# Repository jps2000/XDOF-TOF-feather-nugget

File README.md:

# XDOF-TOF-feather-nugget
Feather nugget (piggyback PCB)  with BNO080/BNO055 IMU BMP388 Baro and VL53L1X tof sensor

Small PCB that fits to feather interface. Tested with nrf52832 BLE4.2
Features
-	9DOF IMU BNO080 or BNO055 optional
-	BMP388  Sensor for height measurements
-	TOF sensor VL53L1X up to 4 meters
-	1 neopixel status LED
-	ON/ OFF toggle button for battery use; USB auto on, shtdown from controller
-	Fits inside the feather footprint

Open source hardware, producers and suggestions welcome

feather nrf52832:  To achieve lowest battery current in off it is recommendend to remove the 100k pullup on EN (R5) and to replace the MBR120 shottky diode (D5) by a SI diode (1N4148).

The housing (not for TOF sensors)  is 3D printed. The cover should be made of transparent or translucent materials Use four screws ,Flat head, stainless steel 16mm long 2.2 mm diameter. The  battery is a Lipo size 502035 with 350mAh. Attention: wrong battery polarity destroys the feather. (Top view feather : GND = left VCC  = right)
Use a Kapton tape and double glue tape between the feather board and the battery.
The button can be made of a 2mm nylon Cylinder head screw colored with an Edding 3000 pen.

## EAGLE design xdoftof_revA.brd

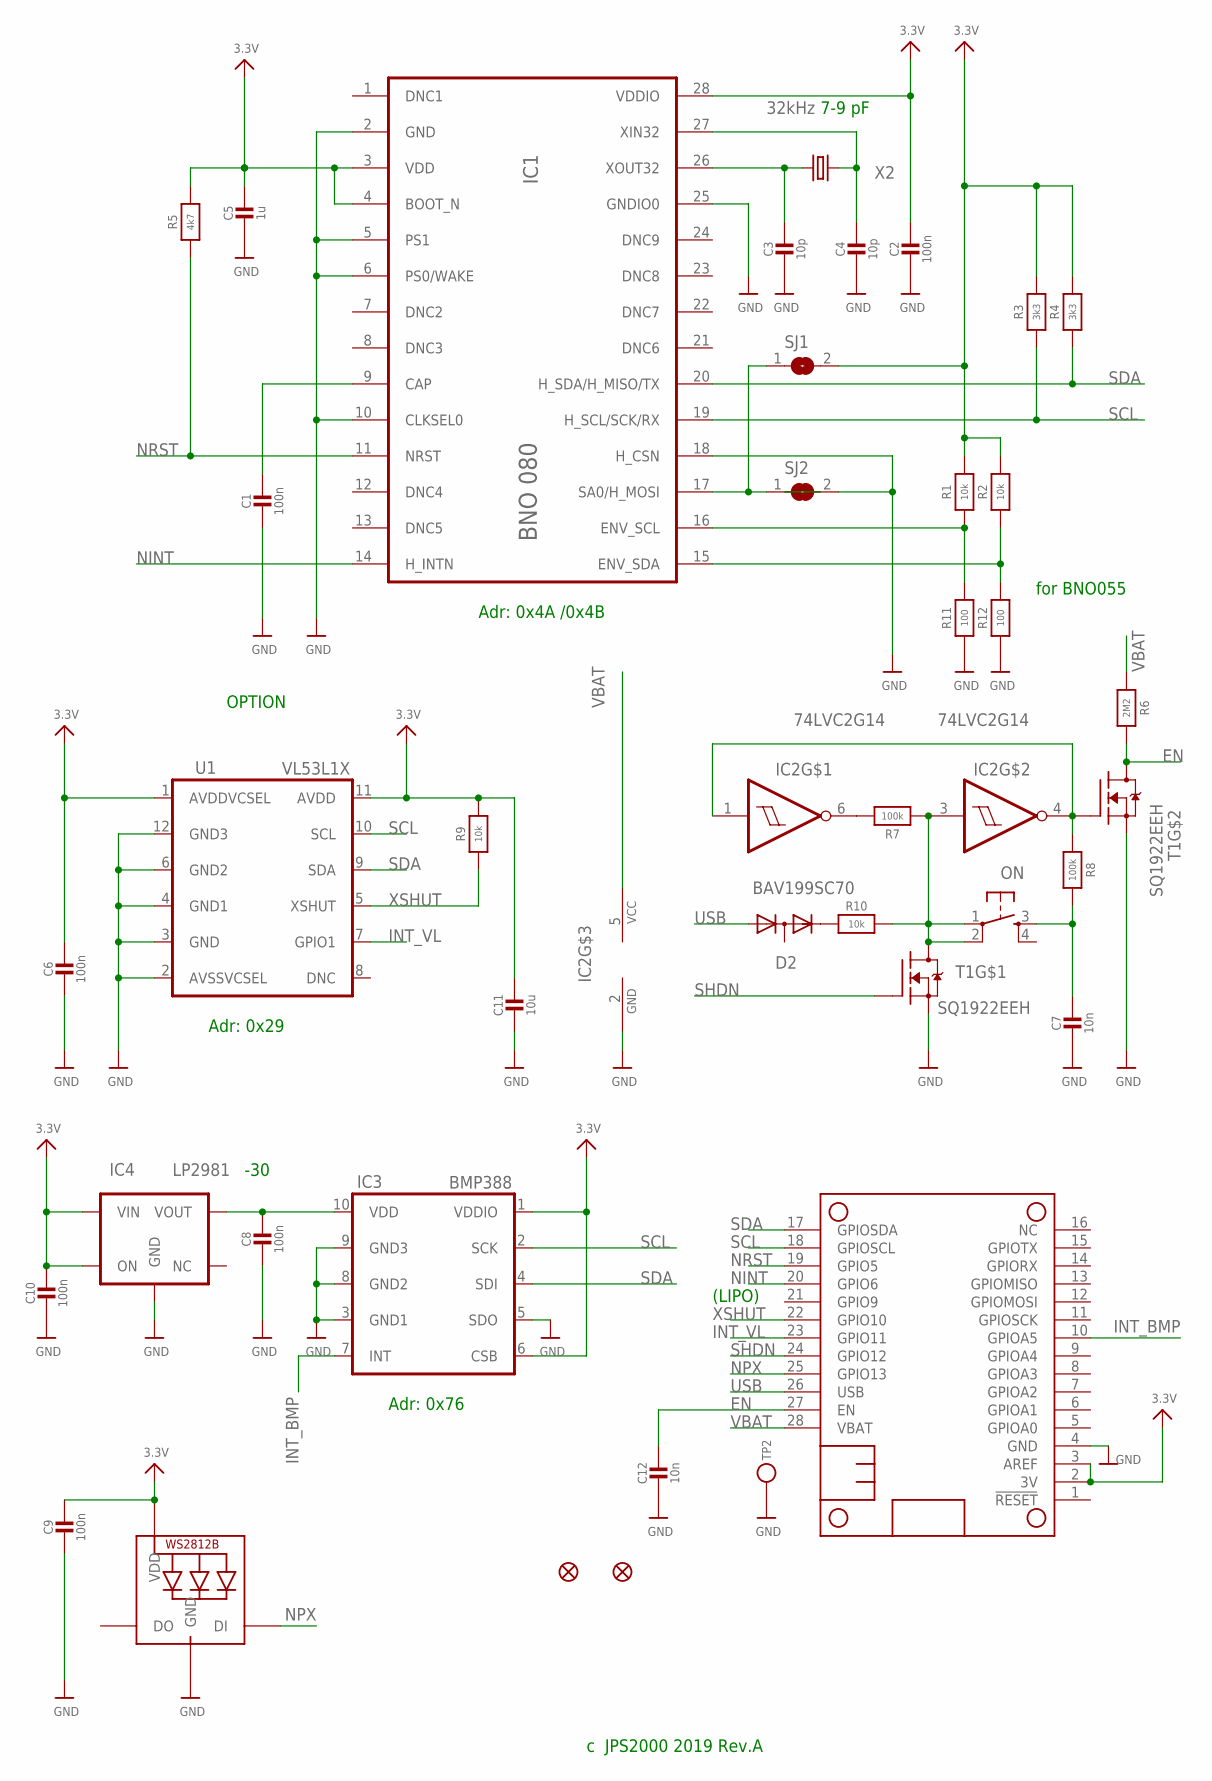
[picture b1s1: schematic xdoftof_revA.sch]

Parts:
C1, C2, C6, C8, C9, C10: 100n; 0603-NO
C3, C4: 10p; 0603-NO
C5: 1u; 0603-NO
C7, C12: 10n; 0603-NO
C11: 10u; 0603-NO
D2: BAV199SC70; SC70
FID1, FID2: FIDUCIAL""; FIDUCIAL_1MM
IC1: BNO080; LGA28
IC2: 74LVC2G14; SC70-6
IC3: BMP388; LGA10
IC4: LP2981; SOT23-5_NEW
LED1: WS2812B3535; LED3535
MS1: FEATHERWING_NOHOLES
ON: ON/OFF; TACTSWSKQGABE010
R1, R2, R9, R10: 10k; _0603MP
R3, R4: 3k3; _0603MP
R5: 4k7; _0603MP
R6: 2M2; _0603MP
R7, R8: 100k; _0603MP
R11, R12: 100; _0603MP
SJ1: SOLDERJUMPERREFLOW_NOPASTE; SOLDERJUMPER_REFLOW_NOPASTE
SJ2: SOLDERJUMPERCLOSED; SOLDERJUMPER_CLOSEDWIRE
T1: SQ1922EEH; SC70-6
TP2: TESTPOINTROUND1MM; TESTPOINT_ROUND_1MM
U1: VL53L1X
X2: 32kHz; XTAL_SMD1

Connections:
3.3V: C2.1, C5.1, C6.1, C9.1, C10.1, C11.1, IC1.3 (VDD), IC1.4 (BOOT_N), IC1.28 (VDDIO), IC3.1 (VDDIO), IC3.6 (CSB), IC4.P$1 (VIN), IC4.P$3 (ON), LED1.2 (VDD), MS1.2 (3V), MS1.3 (AREF), R1.2, R2.2, R3.2, R4.2, R5.2, R9.2, SJ1.2, U1.1 (AVDDVCSEL), U1.11 (AVDD)
EN: C12.1, MS1.27 (EN), R6.2, T1.3 (D)
GND: C1.2, C2.2, C3.2, C4.2, C5.2, C6.2, C7.2, C8.2, C9.2, C10.2, C11.2, C12.2, IC1.2 (GND), IC1.5 (PS1), IC1.6 (PS0/WAKE), IC1.10 (CLKSEL0), IC1.18 (H_CSN), IC1.25 (GNDIO0), IC2.2 (GND), IC3.3 (GND1), IC3.5 (SDO), IC3.8 (GND2), IC3.9 (GND3), IC4.P$2 (GND), LED1.4 (GND), MS1.4 (GND), R11.1, R12.1, SJ2.2, T1.1 (S), T1.4 (S), TP2.P$1, U1.2 (AVSSVCSEL), U1.3 (GND), U1.4 (GND1), U1.6 (GND2), U1.12 (GND3)
INT_BMP: IC3.7 (INT), MS1.10 (GPIOA5)
INT_VL: MS1.23 (GPIO11), U1.7 (GPIO1)
unnamed: C8.1, IC3.10 (VDD), IC4.P$5 (VOUT)
unnamed: C4.1, IC1.27 (XIN32), X2.P$2 (2)
unnamed: C3.1, IC1.26 (XOUT32), X2.P$1 (1)
unnamed: IC1.16 (ENV_SCL), R1.1, R11.2
unnamed: IC1.15 (ENV_SDA), R2.1, R12.2
unnamed: IC2.6 (O), R7.2
unnamed: C1.1, IC1.9 (CAP)
unnamed: D2.2 (C), R10.1
unnamed: IC2.3 (I), ON.1, ON.2, R7.1, R10.2, T1.6 (D)
unnamed: IC1.17 (SA0/H_MOSI), SJ1.1, SJ2.1
unnamed: C7.1, ON.3, R8.2
unnamed: IC2.1 (I), IC2.4 (O), R8.1, T1.5 (G)
NINT: IC1.14 (H_INTN), MS1.20 (GPIO6)
NPX: LED1.1 (DI), MS1.25 (GPIO13)
NRST: IC1.11 (NRST), MS1.19 (GPIO5), R5.1
SCL: IC1.19 (H_SCL/SCK/RX), IC3.2 (SCK), MS1.18 (GPIOSCL), R3.1, U1.10 (SCL)
SDA: IC1.20 (H_SDA/H_MISO/TX), IC3.4 (SDI), MS1.17 (GPIOSDA), R4.1, U1.9 (SDA)
SHDN: MS1.24 (GPIO12), T1.2 (G)
USB: D2.1 (A), MS1.26 (USB)
VBAT: IC2.5 (VCC), MS1.28 (VBAT), R6.1
XSHUT: MS1.22 (GPIO10), R9.1, U1.5 (XSHUT)

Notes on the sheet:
OPTION
(LIPO)
Adr: 0x76
7-9 pF
c JPS2000 2019 Rev.A
-30
Adr: 0x29
Adr: 0x4A /0x4B
for BNO055

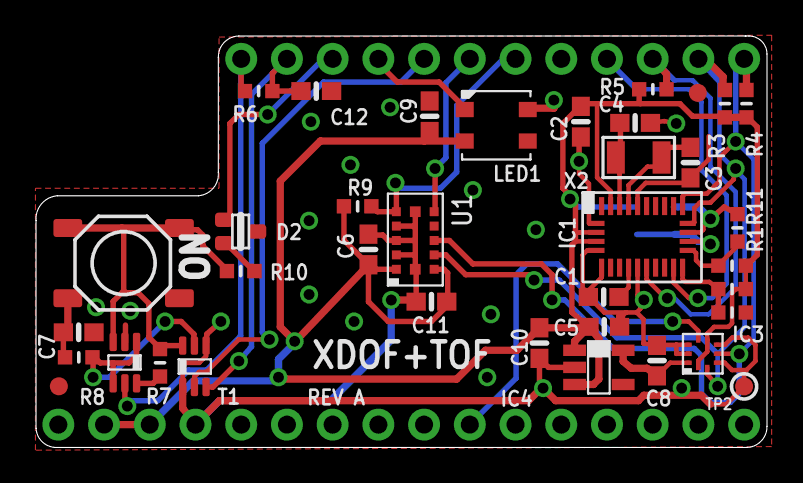
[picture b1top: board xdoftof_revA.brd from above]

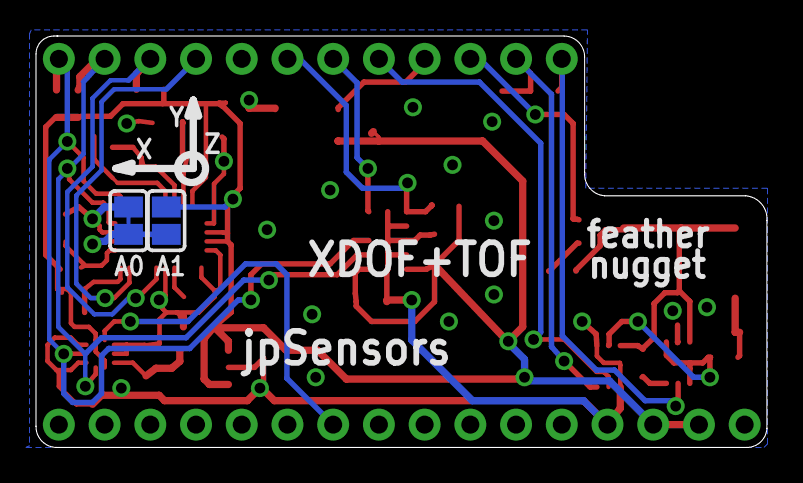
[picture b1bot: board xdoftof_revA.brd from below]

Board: 2 copper layers, 40.6 x 22.9 mm, 42 parts (3 on the bottom side), 26 nets.

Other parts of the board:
U$36, U$37: OPENSOURCE

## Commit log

2021-02-23 Add files via upload
    These are the parts for the housing. The cover should be printed with transparent or translucent material to let the LED´s shine through.
